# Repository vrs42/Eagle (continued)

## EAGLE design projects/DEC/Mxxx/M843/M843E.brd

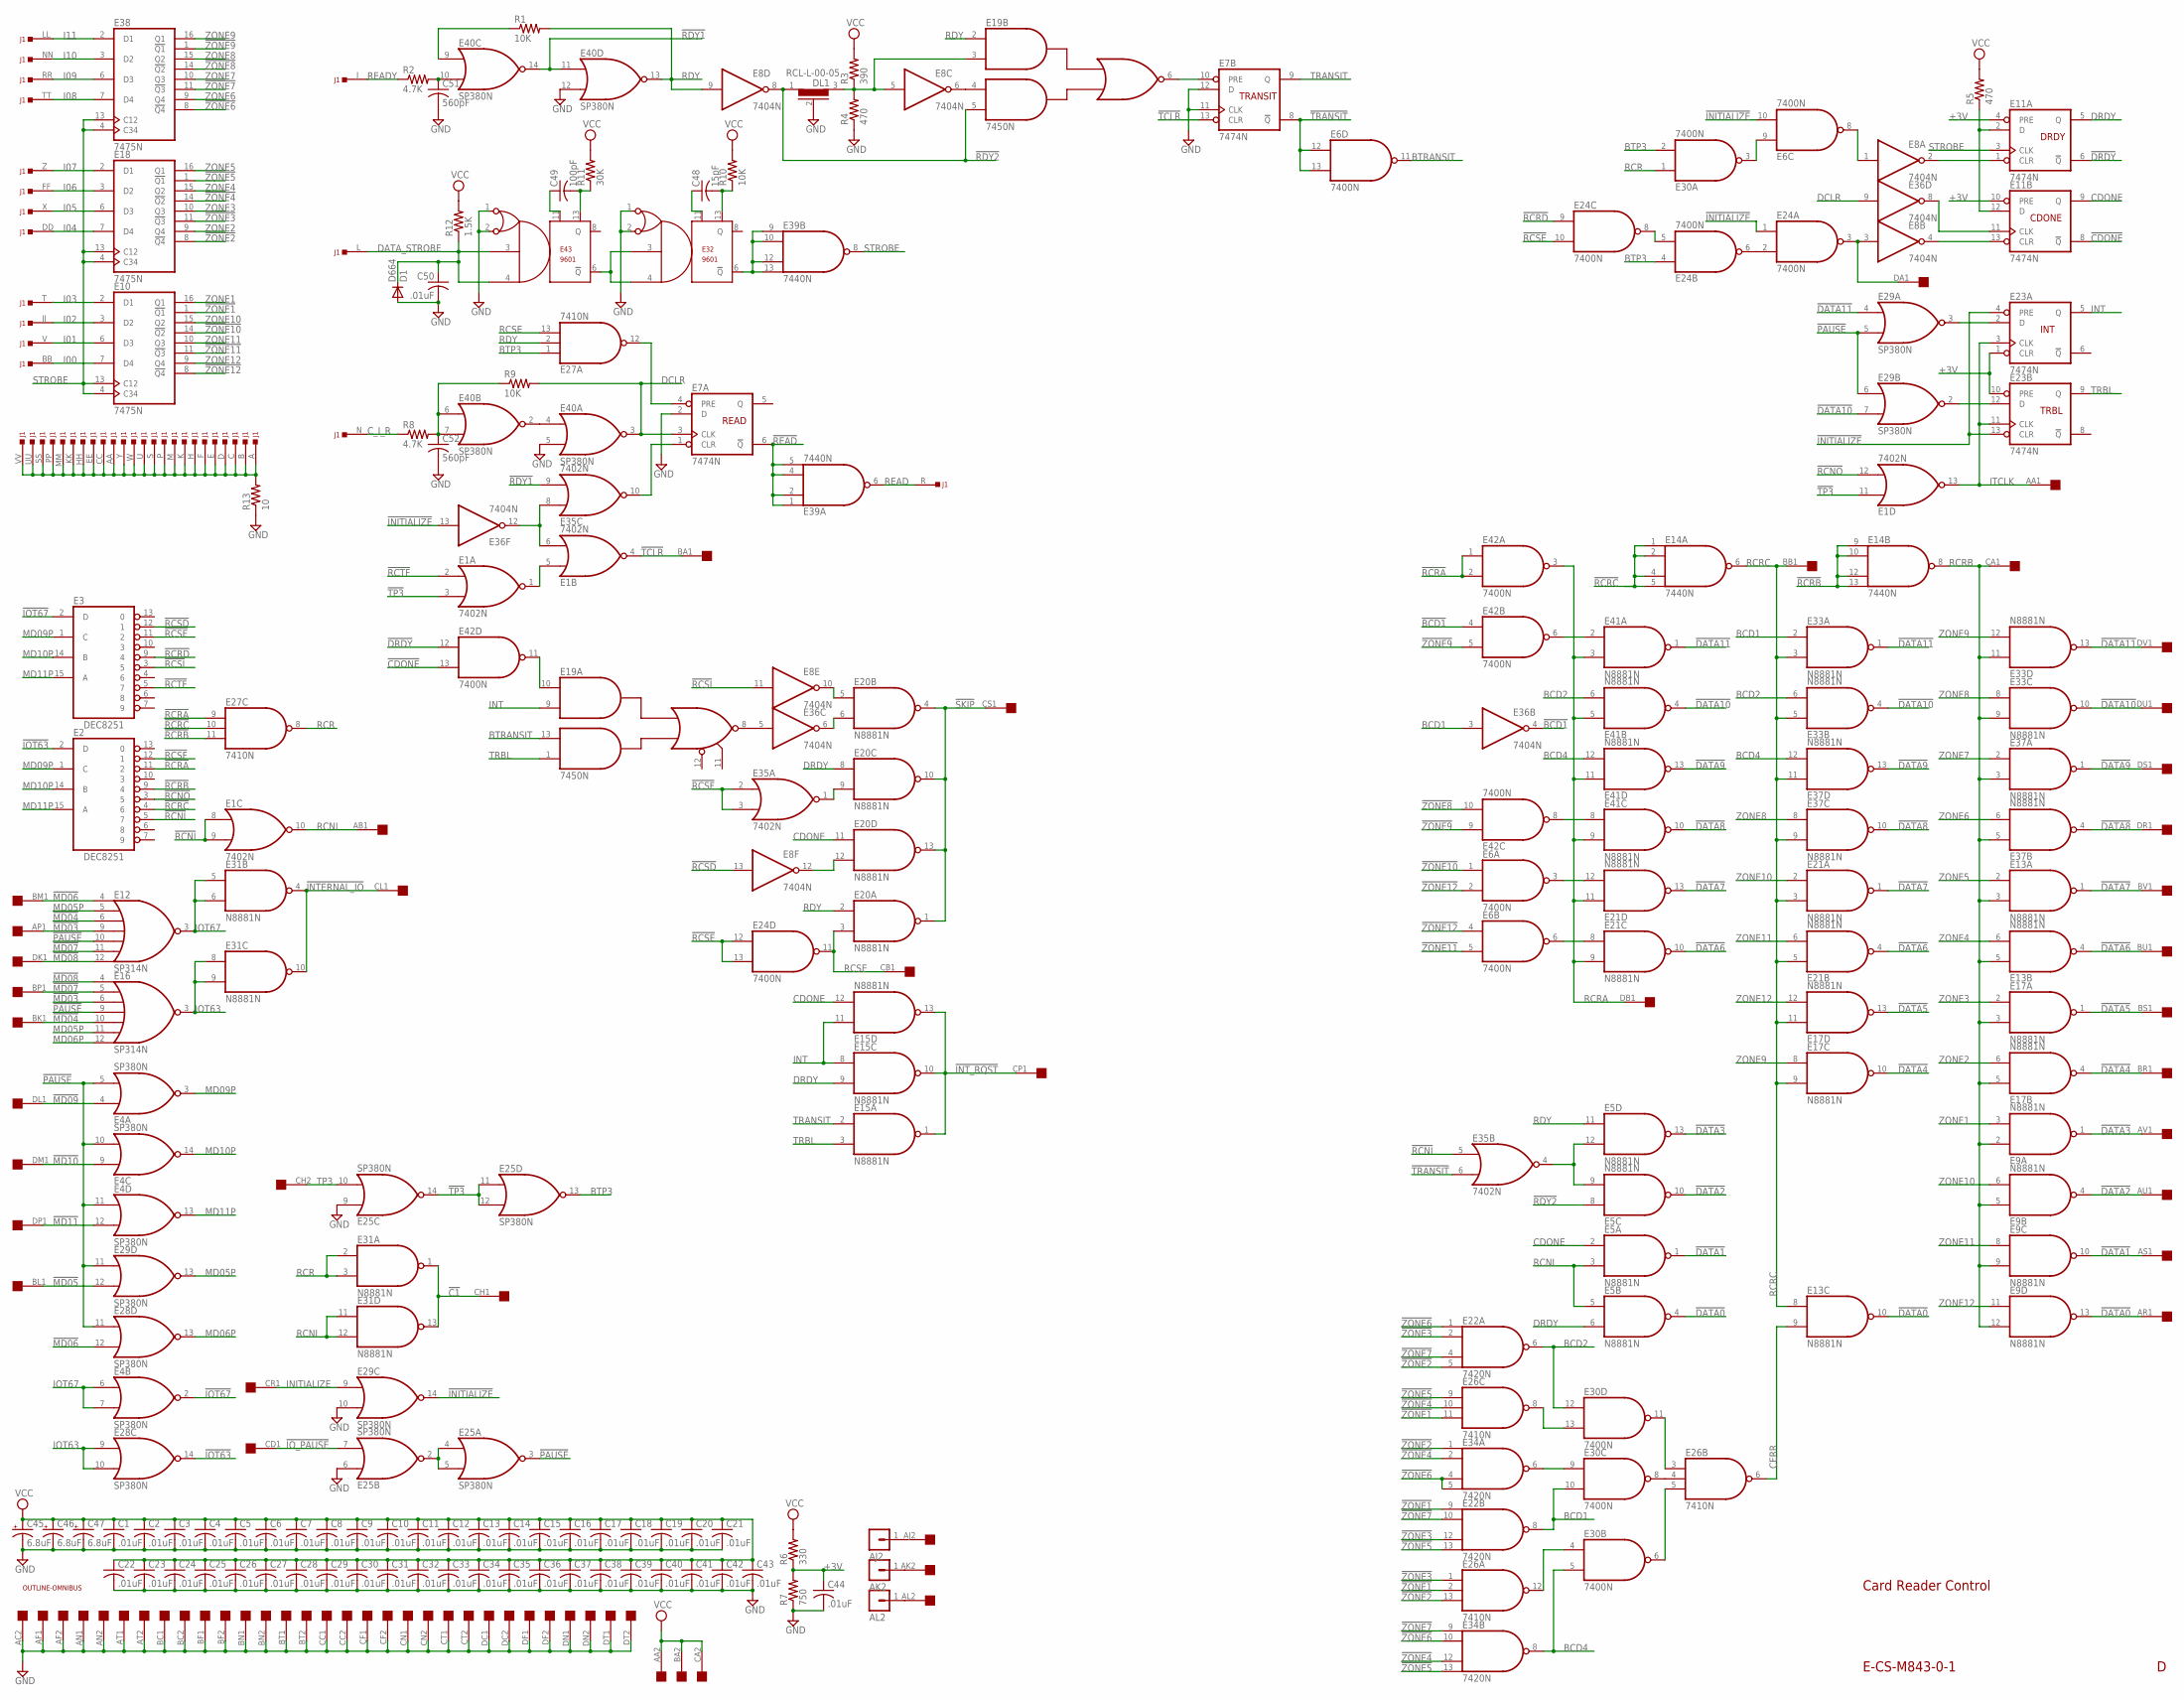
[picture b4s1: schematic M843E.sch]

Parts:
AJ2: MA01-1
AK2: MA01-1
AL2: MA01-1
C1, C6: .01uF; C075-032X103
C2, C3, C4, C5, C7, C8, C9, C10, C11, C12, C13, C14, C15, C16, C17, C18, C19, C20, C21, C22, C23, C24, C25, C26, C27, C28, C29, C30, C31, C32, C33, C34, C35, C36, C37, C38, C39, C40, C41, C42, C43, C44, C50: .01uF; C063-025X075
C45, C46, C47: 6.8uF; E12-8
C48: 15pF; C075-032X103
C49: 100pF; C075-032X103
C51, C52: 560pF; C075-032X103
D1: D664; DO35-10
DL1: RCL-L-00-05
E1, E35: 7402N; DIL14
E2, E3: DEC8251; DIL16
E4, E25, E28, E29, E40: SP380N; DIL14
E5, E9, E13, E15, E17, E20, E21, E31, E33, E37, E41: N8881N; DIL14
E6, E24, E30, E42: 7400N; DIL14
E7, E11, E23: 7474N; DIL14
E8, E36: 7404N; DIL14
E10, E18, E38: 7475N; DIL16
E12, E16: SP314N; DIL14
E14, E39: 7440N; DIL14
E19: 7450N; DIL14
E22, E34: 7420N; DIL14
E26, E27: 7410N; DIL14
E32, E43: 9601; DIL14
EDGE: OMNIBUS; EDGE-CON8
J1: DEC40PINSH; DEC40PINH
R1, R9, R10: 10K; 0207/10
R2, R8: 4.7K; 0207/10
R3: 390; 0207/10
R4, R5: 470; 0207/10
R6: 330; 0207/10
R7: 750; 0207/10
R11: 30K; 0207/10
R12: 1.5K; 0207/10
R13: 10; 0207/10
U$4: OUTLINE-OMNIBUS; OMNIBUS

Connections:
!BCD1: E36.4 (O), E42.4 (I0)
!C1: E31.1 (O), E31.13 (O), EDGE.CH1
!CDONE: E11.8 (!Q), E42.13 (I1)
!DATA0: E5.4 (O), E9.13 (O), E13.10 (O), EDGE.AR1
!DATA1: E5.1 (O), E9.10 (O), EDGE.AS1
!DATA2: E5.10 (O), E9.4 (O), EDGE.AU1
!DATA3: E5.13 (O), E9.1 (O), EDGE.AV1
!DATA4: E17.4 (O), E17.10 (O), EDGE.BR1
!DATA5: E17.1 (O), E17.13 (O), EDGE.BS1
!DATA6: E13.4 (O), E21.4 (O), E21.10 (O), EDGE.BU1
!DATA7: E13.1 (O), E21.1 (O), E21.13 (O), EDGE.BV1
!DATA8: E37.4 (O), E37.10 (O), E41.10 (O), EDGE.DR1
!DATA9: E37.1 (O), E37.13 (O), E41.13 (O), EDGE.DS1
!DATA10: E29.7 (I1), E33.4 (O), E33.10 (O), E41.4 (O), EDGE.DU1
!DATA11: E29.4 (I0), E33.1 (O), E33.13 (O), E41.1 (O), EDGE.DV1
!DRDY: E11.6 (!Q), E42.12 (I0)
!INITIALIZE: E6.10 (I1), E23.4 (PRE), E23.13 (CLR), E24.1 (I0), E29.14 (O), E36.13 (I)
!INTERNAL_IO: E31.4 (O), E31.10 (O), EDGE.CL1
!INT_RQST: E15.1 (O), E15.10 (O), E15.13 (O), EDGE.CP1
!IOT63: E2.2 (D), E28.14 (O)
!IOT67: E3.2 (D), E4.2 (O)
!IO_PAUSE: E25.7 (I1), EDGE.CD1
!MD03: E12.9 (I3), E16.6 (I2), EDGE.AP1
!MD04: E12.6 (I2), E16.10 (I4), EDGE.BK1
!MD05: E29.12 (I1), EDGE.BL1
!MD06: E12.4 (I0), E28.12 (I1), EDGE.BM1
!MD07: E12.11 (I5), E16.5 (I1), EDGE.BP1
!MD08: E12.12 (I6), E16.4 (I0), EDGE.DK1
!MD09: E4.4 (I0), EDGE.DL1
!MD10: E4.9 (I0), EDGE.DM1
!MD11: E4.12 (I1), EDGE.DP1
!PAUSE: E4.5 (I1), E4.10 (I1), E4.11 (I0), E12.10 (I4), E16.9 (I3), E25.3 (O), E28.11 (I0), E29.5 (I1), E29.6 (I0), E29.11 (I0)
!RCNI: E1.8 (I0), E1.9 (I1), E2.5 (7), E35.5 (I0)
!RCNO: E1.12 (I1), E2.3 (5)
!RCRA: E2.11 (2), E27.9 (I0), E42.1 (I0), E42.2 (I1)
!RCRB: E2.9 (4), E14.9 (I0), E14.10 (I1), E14.12 (I2), E14.13 (I3), E27.11 (I2)
!RCRC: E2.4 (6), E14.1 (I0), E14.2 (I1), E14.4 (I2), E14.5 (I3), E27.10 (I1)
!RCRD: E3.9 (4), E24.9 (I0)
!RCSD: E3.12 (1), E8.13 (I)
!RCSE: E3.11 (2), E24.10 (I1), E24.12 (I0), E24.13 (I1)
!RCSF: E2.12 (1), E35.2 (I0), E35.3 (I1)
!RCSI: E3.3 (5), E8.11 (I)
!RCTF: E1.2 (I0), E3.5 (7)
!RDY1: E35.9 (I1), E40.11 (I0), E40.14 (O)
!RDY2: DL1.1, E5.8 (I0), E8.8 (O), E19.5 (I4)
!READ: E7.6 (!Q), E39.1 (I0), E39.2 (I1), E39.4 (I2), E39.5 (I3)
!SKIP: E20.1 (O), E20.4 (O), E20.10 (O), E20.13 (O), EDGE.CS1
!TCLR: E1.4 (O), E7.13 (CLR), EDGE.BA1
!TP3: E1.3 (I1), E1.11 (I0), E25.11 (I0), E25.12 (I1), E25.14 (O)
!TRANSIT: E6.12 (I0), E6.13 (I1), E7.8 (!Q), E35.6 (I1)
!ZONE1: E10.1 (!Q1), E22.9 (I0), E26.2 (I1), E26.11 (I2)
!ZONE2: E18.8 (!Q4), E22.5 (I3), E26.13 (I2), E34.1 (I0)
!ZONE3: E18.11 (!Q3), E22.2 (I1), E22.12 (I2), E26.1 (I0)
!ZONE4: E18.14 (!Q2), E26.10 (I1), E34.2 (I1), E34.12 (I2)
!ZONE5: E18.1 (!Q1), E22.13 (I3), E26.9 (I0), E34.13 (I3)
!ZONE6: E22.1 (I0), E34.4 (I2), E34.5 (I3), E34.10 (I1), E38.8 (!Q4)
!ZONE7: E22.4 (I2), E22.10 (I1), E34.9 (I0), E38.11 (!Q3)
!ZONE8: E38.14 (!Q2), E42.10 (I1)
!ZONE9: E38.1 (!Q1), E42.5 (I1), E42.9 (I0)
!ZONE10: E6.1 (I0), E10.14 (!Q2)
!ZONE11: E6.5 (I1), E10.11 (!Q3)
!ZONE12: E6.2 (I1), E6.4 (I0), E10.8 (!Q4)
+3V: C44.1, E11.4 (PRE), E11.10 (PRE), E23.1 (CLR), E23.10 (PRE), R6.1, R7.2
AJ2: AJ2.1, EDGE.AJ2
AK2: AK2.1, EDGE.AK2
AL2: AL2.1, EDGE.AL2
BCD1: E22.8 (O), E30.10 (I1), E33.2 (I0), E36.3 (I)
BCD2: E22.6 (O), E30.12 (I0), E33.6 (I1), E41.6 (I1)
BCD4: E30.5 (I1), E34.8 (O), E37.12 (I1), E41.12 (I1)
BTP3: E24.4 (I0), E25.13 (O), E27.1 (I0), E30.2 (I1)
BTRANSIT: E6.11 (O), E19.13 (I3)
CDONE: E5.2 (I0), E11.9 (Q), E15.12 (I1), E20.11 (I0)
CERR: E13.9 (I1), E26.6 (O)
C_I_R: J1.N, R8.1
DATA_STROBE: C50.1, D1.C, E43.3, E43.4, J1.L, R12.1
DCLR: E7.3 (CLK), E36.9 (I), E40.3 (O), R9.2
DRDY: E5.6 (I1), E11.5 (Q), E15.9 (I1), E20.8 (I0)
GND: C1.2, C2.2, C3.2, C4.2, C5.2, C6.2, C7.2, C8.2, C9.2, C10.2, C11.2, C12.2, C13.2, C14.2, C15.2, C16.2, C17.2, C18.2, C19.2, C20.2, C21.2, C22.2, C23.2, C24.2, C25.2, C26.2, C27.2, C28.2, C29.2, C30.2, C31.2, C32.2, C33.2, C34.2, C35.2, C36.2, C37.2, C38.2, C39.2, C40.2, C41.2, C42.2, C43.2, C44.2, C45.-, C46.-, C47.-, C50.2, C51.2, C52.2, D1.A, DL1.2, E1.7 (GND), E2.8 (GND), E3.8 (GND), E4.1 (GND), E5.7 (GND), E6.7 (GND), E7.2 (D), E7.7 (GND), E7.11 (CLK), E7.12 (D), E8.7 (GND), E9.7 (GND), E10.12 (GND), E11.7 (GND), E12.1 (GND), E13.7 (GND), E14.7 (GND), E15.7 (GND), E16.1 (GND), E17.7 (GND), E18.12 (GND), E19.7 (GND), E20.7 (GND), E21.7 (GND), E22.7 (GND), E23.7 (GND), E24.7 (GND), E25.1 (GND), E25.6 (I0), E25.9 (I0), E26.7 (GND), E27.7 (GND), E28.1 (GND), E29.1 (GND), E29.10 (I1), E30.7 (GND), E31.7 (GND), E32.1, E32.2, E32.7 (GND), E33.7 (GND), E34.7 (GND), E35.7 (GND), E36.7 (GND), E37.7 (GND), E38.12 (GND), E39.7 (GND), E40.1 (GND), E40.5 (I1), E40.12 (I1), E41.7 (GND), E42.7 (GND), E43.1, E43.2, E43.7 (GND), EDGE.AC2, EDGE.AF1, EDGE.AF2, EDGE.AN1, EDGE.AN2, EDGE.AT1, EDGE.AT2, EDGE.BC1, EDGE.BC2, EDGE.BF1, EDGE.BF2, EDGE.BN1, EDGE.BN2, EDGE.BT1, EDGE.BT2, EDGE.CC1, EDGE.CC2, EDGE.CF1, EDGE.CF2, EDGE.CN1, EDGE.CN2, EDGE.CT1, EDGE.CT2, EDGE.DC1, EDGE.DC2, EDGE.DF1, EDGE.DF2, EDGE.DN1, EDGE.DN2, EDGE.DT1, EDGE.DT2, R4.1, R7.1, R13.1
I00: E10.7 (D4), J1.BB
I01: E10.6 (D3), J1.V
I02: E10.3 (D2), J1.JJ
I03: E10.2 (D1), J1.T
I04: E18.7 (D4), J1.DD
I05: E18.6 (D3), J1.X
I06: E18.3 (D2), J1.FF
I07: E18.2 (D1), J1.Z
I08: E38.7 (D4), J1.TT
I09: E38.6 (D3), J1.RR
I10: E38.3 (D2), J1.NN
I11: E38.2 (D1), J1.LL
INITIALIZE: E29.9 (I0), EDGE.CR1
INT: E15.8 (I0), E15.11 (I0), E19.9 (I2), E23.5 (Q)
IOT63: E16.3 (O), E28.9 (I0), E28.10 (I1), E31.8 (I0), E31.9 (I1)
IOT67: E4.6 (I0), E4.7 (I1), E12.3 (O), E31.5 (I0), E31.6 (I1)
ITCLK: E1.13 (O), E23.3 (CLK), E23.11 (CLK), EDGE.AA1
MD05P: E12.5 (I1), E16.11 (I5), E29.13 (O)
MD06P: E16.12 (I6), E28.13 (O)
MD09P: E2.1 (C), E3.1 (C), E4.3 (O)
MD10P: E2.14 (B), E3.14 (B), E4.14 (O)
MD11P: E2.15 (A), E3.15 (A), E4.13 (O)
unnamed: E26.3 (I0), E30.11 (O)
unnamed: E25.2 (O), E25.4 (I0), E25.5 (I1)
unnamed: E11.11 (CLK), E36.8 (O)
unnamed: E6.8 (O), E8.1 (I)
unnamed: E5.9 (I1), E5.12 (I1), E35.4 (O)
unnamed: E32.6 (!Q), E39.9 (I0), E39.10 (I1), E39.12 (I2), E39.13 (I3)
unnamed: E32.3, E32.4, E43.6 (!Q)
unnamed: E26.4 (I1), E30.8 (O)
unnamed: C49.2, E43.13, R11.1
unnamed: E30.9 (I0), E34.6 (O)
unnamed: C49.1, E43.11
unnamed: C48.2, E32.13, R10.1
unnamed: C52.1, E40.6 (I0), E40.7 (I1), R8.2, R9.1
unnamed: C48.1, E32.11
unnamed: E19.8 (O), E36.5 (I)
unnamed: E40.2 (O), E40.4 (I0)
unnamed: C51.1, E40.10 (I1), R2.2
unnamed: E26.5 (I2), E30.6 (O)
unnamed: E6.3 (O), E21.12 (I1)
unnamed: E41.2 (I0), E42.6 (O)
unnamed: DL1.3, E8.5 (I), E19.3 (I2), R3.1, R4.2
unnamed: E6.6 (O), E21.8 (I0)
unnamed: E41.8 (I0), E42.8 (O)
unnamed: E40.9 (I0), R1.1
unnamed: E8.6 (O), E19.4 (I3)
unnamed: E8.4 (O), E11.13 (CLR)
unnamed: E8.3 (I), E24.3 (O), EDGE.DA1
unnamed: E6.9 (I0), E30.3 (O)
unnamed: E8.2 (O), E11.1 (CLR)
unnamed: E7.10 (PRE), E19.6 (O)
unnamed: E26.12 (O), E30.4 (I0)
unnamed: E26.8 (O), E30.13 (I1)
unnamed: E11.2 (D), E11.12 (D), R5.1
unnamed: E7.1 (CLR), E35.10 (O)
unnamed: J1.A, J1.AA, J1.B, J1.C, J1.CC, J1.D, J1.E, J1.EE, J1.F, J1.H, J1.HH, J1.K, J1.KK, J1.M, J1.MM, J1.P, J1.PP, J1.S, J1.SS, J1.U, J1.UU, J1.VV, J1.W, J1.Y, R13.2
unnamed: E23.2 (D), E29.3 (O)
unnamed: E7.4 (PRE), E27.12 (O)
unnamed: E20.6 (I1), E36.6 (O)
unnamed: E19.10 (I1), E42.11 (O)
unnamed: E24.2 (I1), E24.6 (O)
unnamed: E20.9 (I1), E35.1 (O)
unnamed: E8.12 (O), E20.12 (I1)
unnamed: E1.6 (I1), E35.8 (I0), E36.12 (O)
unnamed: E23.12 (D), E29.2 (O)
unnamed: E1.1 (O), E1.5 (I0)
unnamed: E24.5 (I1), E24.8 (O)
RCNI: E1.10 (O), E5.3 (I1), E5.5 (I0), E31.11 (I0), E31.12 (I1), EDGE.AB1
RCR: E27.8 (O), E30.1 (I0), E31.2 (I0), E31.3 (I1)
RCRA: E21.9 (I1), E21.11 (I0), E41.3 (I1), E41.5 (I0), E41.9 (I1), E41.11 (I0), E42.3 (O), EDGE.DB1
RCRB: E9.2 (I0), E9.5 (I0), E9.9 (I1), E9.12 (I1), E13.3 (I1), E13.5 (I0), E14.8 (O), E17.3 (I1), E17.5 (I0), E33.9 (I1), E33.11 (I0), E37.3 (I1), E37.5 (I0), EDGE.CA1
RCRC: E13.8 (I0), E14.6 (O), E17.9 (I1), E17.11 (I0), E21.3 (I1), E21.5 (I0), E33.3 (I1), E33.5 (I0), E37.9 (I1), E37.11 (I0), EDGE.BB1
RCSE: E20.3 (I1), E24.11 (O), E27.13 (I2), EDGE.CB1
RCSI: E8.10 (O), E20.5 (I0)
RDY: E5.11 (I0), E8.9 (I), E19.2 (I1), E20.2 (I0), E27.2 (I1), E40.13 (O), R1.2
READ: E39.6 (O), J1.R
READY: J1.J, R2.1
STROBE: E10.4 (C34), E10.13 (C12), E11.3 (CLK), E18.4 (C34), E18.13 (C12), E38.4 (C34), E38.13 (C12), E39.8 (O)
TP3: E25.10 (I1), EDGE.CH2
TRANSIT: E7.9 (Q), E15.2 (I0)
TRBL: E15.3 (I1), E19.1 (I4), E23.9 (Q)
VCC: C1.1, C2.1, C3.1, C4.1, C5.1, C6.1, C7.1, C8.1, C9.1, C10.1, C11.1, C12.1, C13.1, C14.1, C15.1, C16.1, C17.1, C18.1, C19.1, C20.1, C21.1, C22.1, C23.1, C24.1, C25.1, C26.1, C27.1, C28.1, C29.1, C30.1, C31.1, C32.1, C33.1, C34.1, C35.1, C36.1, C37.1, C38.1, C39.1, C40.1, C41.1, C42.1, C43.1, C45.+, C46.+, C47.+, E1.14 (VCC), E2.16 (VCC), E3.16 (VCC), E4.8 (VCC), E5.14 (VCC), E6.14 (VCC), E7.14 (VCC), E8.14 (VCC), E9.14 (VCC), E10.5 (VCC), E11.14 (VCC), E12.8 (VCC), E13.14 (VCC), E14.14 (VCC), E15.14 (VCC), E16.8 (VCC), E17.14 (VCC), E18.5 (VCC), E19.14 (VCC), E20.14 (VCC), E21.14 (VCC), E22.14 (VCC), E23.14 (VCC), E24.14 (VCC), E25.8 (VCC), E26.14 (VCC), E27.14 (VCC), E28.8 (VCC), E29.8 (VCC), E30.14 (VCC), E31.14 (VCC), E32.14 (VCC), E33.14 (VCC), E34.14 (VCC), E35.14 (VCC), E36.14 (VCC), E37.14 (VCC), E38.5 (VCC), E39.14 (VCC), E40.8 (VCC), E41.14 (VCC), E42.14 (VCC), E43.14 (VCC), EDGE.AA2, EDGE.BA2, EDGE.CA2, R3.2, R5.2, R6.2, R10.2, R11.2, R12.2
ZONE1: E9.3 (I1), E10.16 (Q1)
ZONE2: E17.6 (I1), E18.9 (Q4)
ZONE3: E17.2 (I0), E18.10 (Q3)
ZONE4: E13.6 (I1), E18.15 (Q2)
ZONE5: E13.2 (I0), E18.16 (Q1)
ZONE6: E37.6 (I1), E38.9 (Q4)
ZONE7: E37.2 (I0), E38.10 (Q3)
ZONE8: E33.8 (I0), E37.8 (I0), E38.15 (Q2)
ZONE9: E17.8 (I0), E33.12 (I1), E38.16 (Q1)
ZONE10: E9.6 (I1), E10.15 (Q2), E21.2 (I0)
ZONE11: E9.8 (I0), E10.10 (Q3), E21.6 (I1)
ZONE12: E9.11 (I0), E10.9 (Q4), E17.12 (I1)

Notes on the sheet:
E-CS-M843-0-1
Card Reader Control
TRBL
INT
TRANSIT
CDONE
DRDY
READ

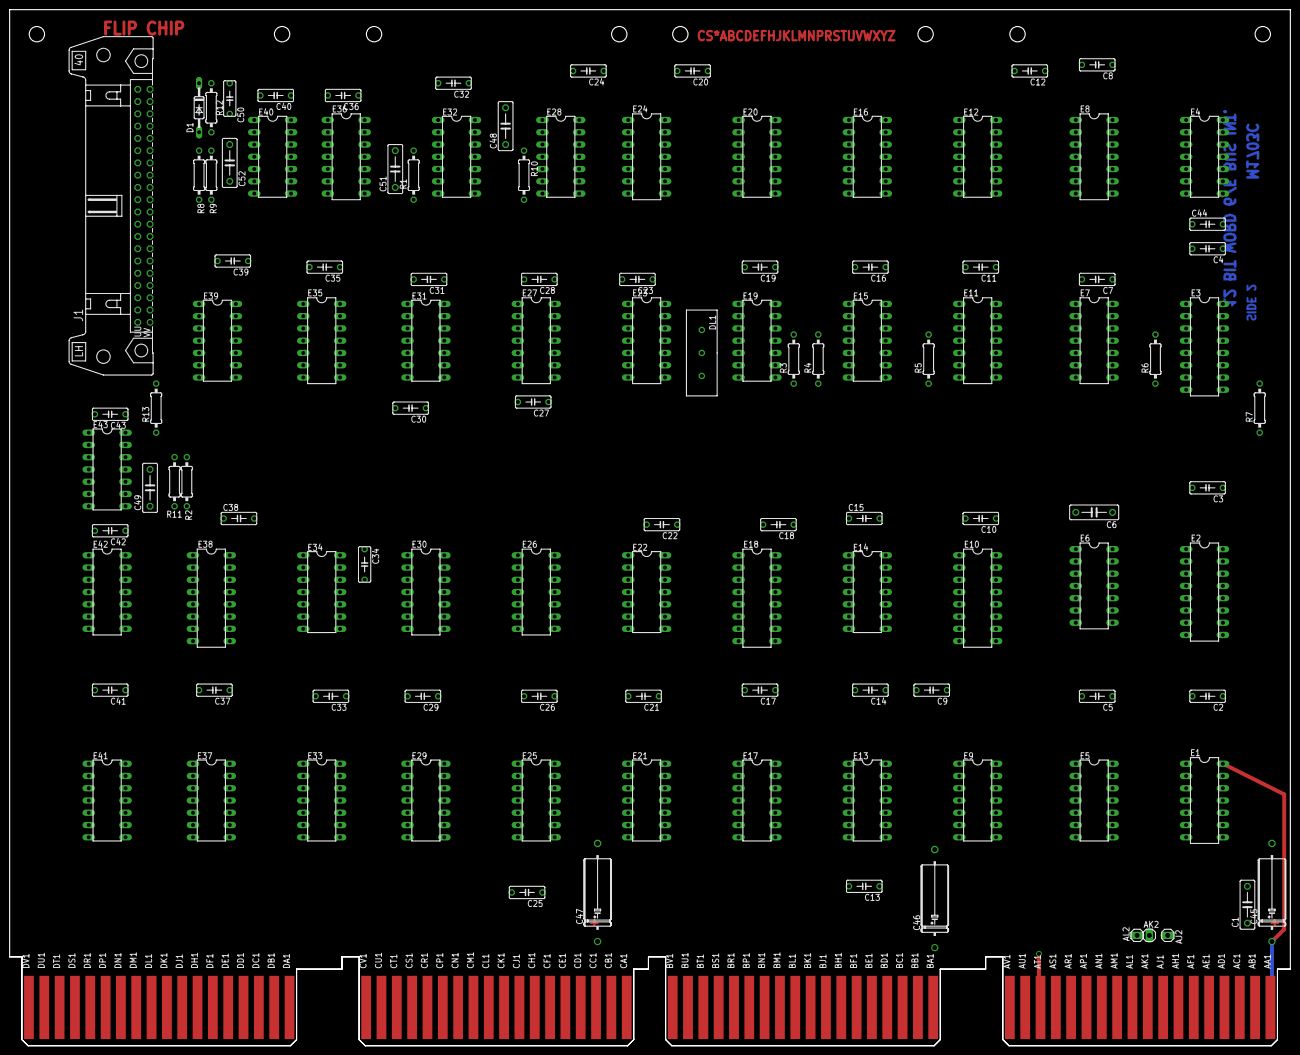
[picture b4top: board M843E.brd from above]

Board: 2 copper layers, 265.3 x 214.6 mm, 117 parts (0 on the bottom side), 173 nets.

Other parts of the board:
U$3: FLIPCHIP

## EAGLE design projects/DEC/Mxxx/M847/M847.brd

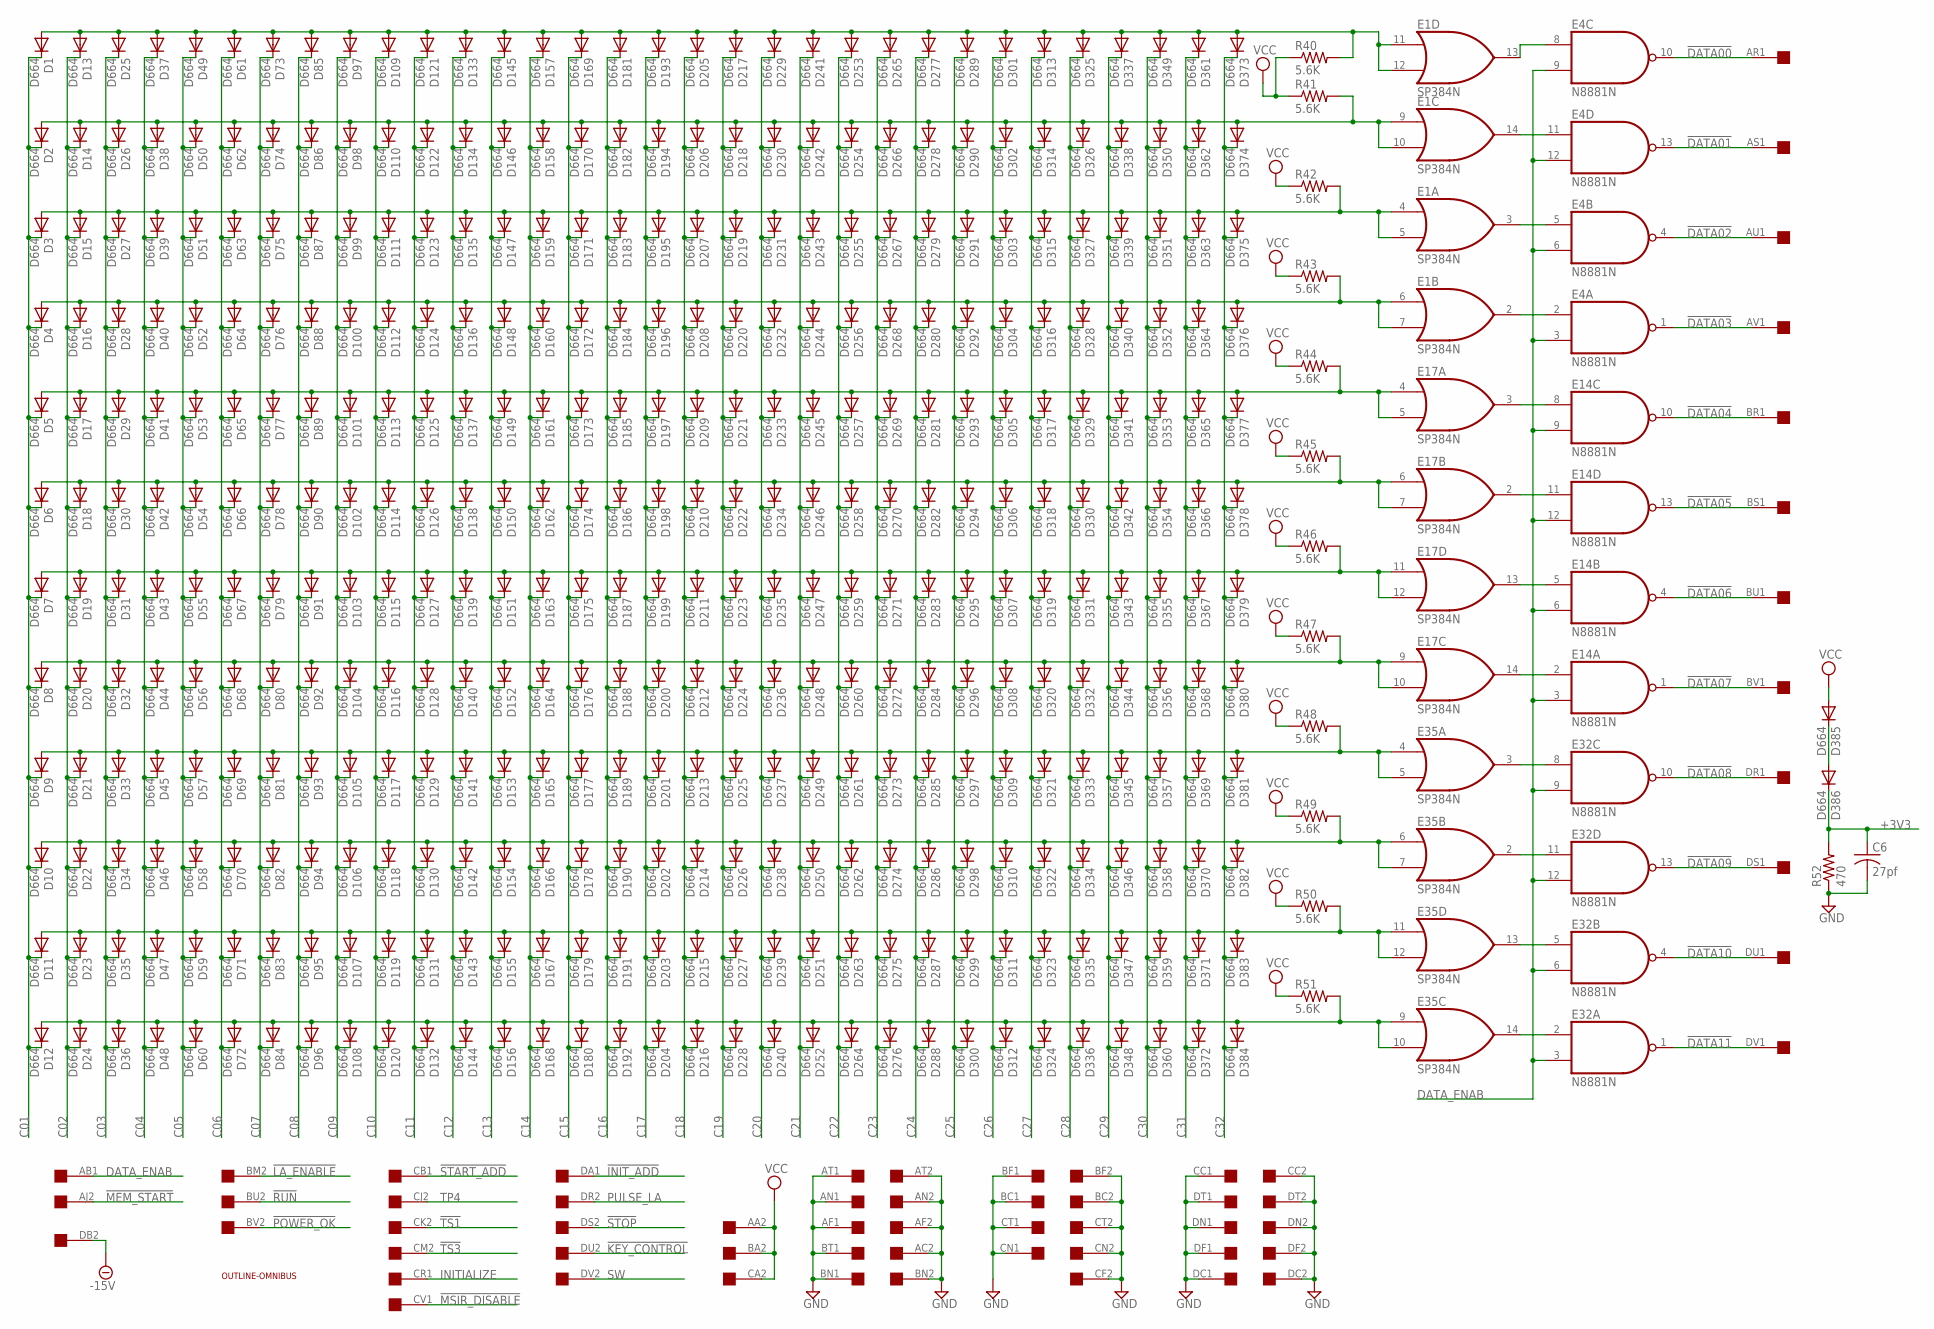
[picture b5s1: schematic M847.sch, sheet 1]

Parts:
C6: 27pf; C050-025X075
D1, D2, D3, D4, D5, D6, D7, D8, D9, D10, D11, D12, D13, D14, D15, D16, D17, D18, D19, D20, D21, D22, D23, D24, D25, D26, D27, D28, D29, D30, D31, D32, D33, D34, D35, D36, D37, D38, D39, D40, D41, D42, D43, D44, D45, D46, D47, D48, D49, D50, D51, D52, D53, D54, D55, D56, D57, D58, D59, D60, D61, D62, D63, D64, D65, D66, D67, D68, D69, D70, D71, D72, D73, D74, D75, D76, D77, D78, D79, D80, D81, D82, D83, D84, D85, D86, D87, D88, D89, D90, D91, D92, D93, D94, D95, D96, D97, D98, D99, D100, D101, D102, D103, D104, D105, D106, D107, D108, D109, D110, D111, D112, D113, D114, D115, D116, D117, D118, D119, D120, D121, D122, D123, D124, D125, D126, D127, D128, D129, D130, D131, D132, D133, D134, D135, D136, D137, D138, D139, D140, D141, D142, D143, D144, D145, D146, D147, D148, D149, D150, D151, D152, D153, D154, D155, D156, D157, D158, D159, D160, D161, D162, D163, D164, D165, D166, D167, D168, D169, D170, D171, D172, D173, D174, D175, D176, D177, D178, D179, D180, D181, D182, D183, D184, D185, D186, D187, D188, D189, D190, D191, D192, D193, D194, D195, D196, D197, D198, D199, D200, D201, D202, D203, D204, D205, D206, D207, D208, D209, D210, D211, D212, D213, D214, D215, D216, D217, D218, D219, D220, D221, D222, D223, D224, D225, D226, D227, D228, D229, D230, D231, D232, D233, D234, D235, D236, D237, D238, D239, D240, D241, D242, D243, D244, D245, D246, D247, D248, D249, D250, D251, D252, D253, D254, D255, D256, D257, D258, D259, D260, D261, D262, D263, D264, D265, D266, D267, D268, D269, D270, D271, D272, D273, D274, D275, D276, D277, D278, D279, D280, D281, D282, D283, D284, D285, D286, D287, D288, D289, D290, D291, D292, D293, D294, D295, D296, D297, D298, D299, D300, D301, D302, D303, D304, D305, D306, D307, D308, D309, D310, D311, D312, D313, D314, D315, D316, D317, D318, D319, D320, D321, D322, D323, D324, D325, D326, D327, D328, D329, D330, D331, D332, D333, D334, D335, D336, D337, D338, D339, D340, D341, D342, D343, D344, D345, D346, D347, D348, D349, D350, D351, D352, D353, D354, D355, D356, D357, D358, D359, D360, D361, D362, D363, D364, D365, D366, D367, D368, D369, D370, D371, D372, D373, D374, D375, D376, D377, D378, D379, D380, D381, D382, D383, D384, D385, D386: D664; DO35-10
E1, E17, E35: SP384N; DIL14
E4, E14, E32: N8881N; DIL14
R40, R41, R42, R43, R44, R45, R46, R47, R48, R49, R50, R51: 5.6K; 0207/10
R52: 470; 0207/10
U$1: OUTLINE-OMNIBUS; OMNIBUS
U$2: QUAD; EDGE-CON8

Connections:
!DATA00: E4.10 (O), U$2.AR1; also elsewhere on the board
!DATA01: E4.13 (O), U$2.AS1; also elsewhere on the board
!DATA02: E4.4 (O), U$2.AU1; also elsewhere on the board
!DATA03: E4.1 (O), U$2.AV1; also elsewhere on the board
!DATA04: E14.10 (O), U$2.BR1; also elsewhere on the board
!DATA05: E14.13 (O), U$2.BS1; also elsewhere on the board
!DATA06: E14.4 (O), U$2.BU1; also elsewhere on the board
!DATA07: E14.1 (O), U$2.BV1; also elsewhere on the board
!DATA08: E32.10 (O), U$2.DR1; also elsewhere on the board
!DATA09: E32.13 (O), U$2.DS1; also elsewhere on the board
!DATA10: E32.4 (O), U$2.DU1; also elsewhere on the board
!DATA11: E32.1 (O), U$2.DV1; also elsewhere on the board
!INIT_ADD: U$2.DA1; also elsewhere on the board
!KEY_CONTROL: U$2.DU2; also elsewhere on the board
!LA_ENABLE: U$2.BM2; also elsewhere on the board
!MEM_START: U$2.AJ2; also elsewhere on the board
!MSIR_DISABLE: U$2.CV1; also elsewhere on the board
!POWER_OK: U$2.BV2; also elsewhere on the board
!RUN: U$2.BU2; also elsewhere on the board
!START_ADD: U$2.CB1; also elsewhere on the board
!STOP: U$2.DS2; also elsewhere on the board
!TS1: U$2.CK2; also elsewhere on the board
!TS3: U$2.CM2; also elsewhere on the board
+3V3: C6.1, D386.C, R52.2; also elsewhere on the board
-15V: U$2.DB2; also elsewhere on the board
C01: D1.C, D2.C, D3.C, D4.C, D5.C, D6.C, D7.C, D8.C, D9.C, D10.C, D11.C, D12.C; also elsewhere on the board
C02: D13.C, D14.C, D15.C, D16.C, D17.C, D18.C, D19.C, D20.C, D21.C, D22.C, D23.C, D24.C; also elsewhere on the board
C03: D25.C, D26.C, D27.C, D28.C, D29.C, D30.C, D31.C, D32.C, D33.C, D34.C, D35.C, D36.C; also elsewhere on the board
C04: D37.C, D38.C, D39.C, D40.C, D41.C, D42.C, D43.C, D44.C, D45.C, D46.C, D47.C, D48.C; also elsewhere on the board
C05: D49.C, D50.C, D51.C, D52.C, D53.C, D54.C, D55.C, D56.C, D57.C, D58.C, D59.C, D60.C; also elsewhere on the board
C06: D61.C, D62.C, D63.C, D64.C, D65.C, D66.C, D67.C, D68.C, D69.C, D70.C, D71.C, D72.C; also elsewhere on the board
C07: D73.C, D74.C, D75.C, D76.C, D77.C, D78.C, D79.C, D80.C, D81.C, D82.C, D83.C, D84.C; also elsewhere on the board
C08: D85.C, D86.C, D87.C, D88.C, D89.C, D90.C, D91.C, D92.C, D93.C, D94.C, D95.C, D96.C; also elsewhere on the board
C09: D97.C, D98.C, D99.C, D100.C, D101.C, D102.C, D103.C, D104.C, D105.C, D106.C, D107.C, D108.C; also elsewhere on the board
C10: D109.C, D110.C, D111.C, D112.C, D113.C, D114.C, D115.C, D116.C, D117.C, D118.C, D119.C, D120.C; also elsewhere on the board
C11: D121.C, D122.C, D123.C, D124.C, D125.C, D126.C, D127.C, D128.C, D129.C, D130.C, D131.C, D132.C; also elsewhere on the board
C12: D133.C, D134.C, D135.C, D136.C, D137.C, D138.C, D139.C, D140.C, D141.C, D142.C, D143.C, D144.C; also elsewhere on the board
C13: D145.C, D146.C, D147.C, D148.C, D149.C, D150.C, D151.C, D152.C, D153.C, D154.C, D155.C, D156.C; also elsewhere on the board
C14: D157.C, D158.C, D159.C, D160.C, D161.C, D162.C, D163.C, D164.C, D165.C, D166.C, D167.C, D168.C; also elsewhere on the board
C15: D169.C, D170.C, D171.C, D172.C, D173.C, D174.C, D175.C, D176.C, D177.C, D178.C, D179.C, D180.C; also elsewhere on the board
C16: D181.C, D182.C, D183.C, D184.C, D185.C, D186.C, D187.C, D188.C, D189.C, D190.C, D191.C, D192.C; also elsewhere on the board
C17: D193.C, D194.C, D195.C, D196.C, D197.C, D198.C, D199.C, D200.C, D201.C, D202.C, D203.C, D204.C; also elsewhere on the board
C18: D205.C, D206.C, D207.C, D208.C, D209.C, D210.C, D211.C, D212.C, D213.C, D214.C, D215.C, D216.C; also elsewhere on the board
C19: D217.C, D218.C, D219.C, D220.C, D221.C, D222.C, D223.C, D224.C, D225.C, D226.C, D227.C, D228.C; also elsewhere on the board
C20: D229.C, D230.C, D231.C, D232.C, D233.C, D234.C, D235.C, D236.C, D237.C, D238.C, D239.C, D240.C; also elsewhere on the board
C21: D241.C, D242.C, D243.C, D244.C, D245.C, D246.C, D247.C, D248.C, D249.C, D250.C, D251.C, D252.C; also elsewhere on the board
C22: D253.C, D254.C, D255.C, D256.C, D257.C, D258.C, D259.C, D260.C, D261.C, D262.C, D263.C, D264.C; also elsewhere on the board
C23: D265.C, D266.C, D267.C, D268.C, D269.C, D270.C, D271.C, D272.C, D273.C, D274.C, D275.C, D276.C; also elsewhere on the board
C24: D277.C, D278.C, D279.C, D280.C, D281.C, D282.C, D283.C, D284.C, D285.C, D286.C, D287.C, D288.C; also elsewhere on the board
C25: D289.C, D290.C, D291.C, D292.C, D293.C, D294.C, D295.C, D296.C, D297.C, D298.C, D299.C, D300.C; also elsewhere on the board
C26: D301.C, D302.C, D303.C, D304.C, D305.C, D306.C, D307.C, D308.C, D309.C, D310.C, D311.C, D312.C; also elsewhere on the board
C27: D313.C, D314.C, D315.C, D316.C, D317.C, D318.C, D319.C, D320.C, D321.C, D322.C, D323.C, D324.C; also elsewhere on the board
C28: D325.C, D326.C, D327.C, D328.C, D329.C, D330.C, D331.C, D332.C, D333.C, D334.C, D335.C, D336.C; also elsewhere on the board
C29: D337.C, D338.C, D339.C, D340.C, D341.C, D342.C, D343.C, D344.C, D345.C, D346.C, D347.C, D348.C; also elsewhere on the board
C30: D349.C, D350.C, D351.C, D352.C, D353.C, D354.C, D355.C, D356.C, D357.C, D358.C, D359.C, D360.C; also elsewhere on the board
C31: D361.C, D362.C, D363.C, D364.C, D365.C, D366.C, D367.C, D368.C, D369.C, D370.C, D371.C, D372.C; also elsewhere on the board
C32: D373.C, D374.C, D375.C, D376.C, D377.C, D378.C, D379.C, D380.C, D381.C, D382.C, D383.C, D384.C; also elsewhere on the board
DATA_ENAB: E4.3 (I1), E4.6 (I1), E4.9 (I1), E4.12 (I1), E14.3 (I1), E14.6 (I1), E14.9 (I1), E14.12 (I1), E32.3 (I1), E32.6 (I1), E32.9 (I1), E32.12 (I1), U$2.AB1; also elsewhere on the board
GND: C6.2, E1.1 (GND), E4.7 (GND), E14.7 (GND), E17.1 (GND), E32.7 (GND), E35.1 (GND), R52.1, U$2.AC2, U$2.AF1, U$2.AF2, U$2.AN1, U$2.AN2, U$2.AT1, U$2.AT2, U$2.BC1, U$2.BC2, U$2.BF1, U$2.BF2, U$2.BN1, U$2.BN2, U$2.BT1, U$2.CC1, U$2.CC2, U$2.CF2, U$2.CN1, U$2.CN2, U$2.CT1, U$2.CT2, U$2.DC1, U$2.DC2, U$2.DF1, U$2.DF2, U$2.DN1, U$2.DN2, U$2.DT1, U$2.DT2; also elsewhere on the board
INITIALIZE: U$2.CR1; also elsewhere on the board
unnamed: D1.A, D13.A, D25.A, D37.A, D49.A, D61.A, D73.A, D85.A, D97.A, D109.A, D121.A, D133.A, D145.A, D157.A, D169.A, D181.A, D193.A, D205.A, D217.A, D229.A, D241.A, D253.A, D265.A, D277.A, D289.A, D301.A, D313.A, D325.A, D337.A, D349.A, D361.A, D373.A, E1.11 (I0), E1.12 (I1), R40.2
unnamed: D12.A, D24.A, D36.A, D48.A, D60.A, D72.A, D84.A, D96.A, D108.A, D120.A, D132.A, D144.A, D156.A, D168.A, D180.A, D192.A, D204.A, D216.A, D228.A, D240.A, D252.A, D264.A, D276.A, D288.A, D300.A, D312.A, D324.A, D336.A, D348.A, D360.A, D372.A, D384.A, E35.9 (I0), E35.10 (I1), R51.2
unnamed: D11.A, D23.A, D35.A, D47.A, D59.A, D71.A, D83.A, D95.A, D107.A, D119.A, D131.A, D143.A, D155.A, D167.A, D179.A, D191.A, D203.A, D215.A, D227.A, D239.A, D251.A, D263.A, D275.A, D287.A, D299.A, D311.A, D323.A, D335.A, D347.A, D359.A, D371.A, D383.A, E35.11 (I0), E35.12 (I1), R50.2
unnamed: D10.A, D22.A, D34.A, D46.A, D58.A, D70.A, D82.A, D94.A, D106.A, D118.A, D130.A, D142.A, D154.A, D166.A, D178.A, D190.A, D202.A, D214.A, D226.A, D238.A, D250.A, D262.A, D274.A, D286.A, D298.A, D310.A, D322.A, D334.A, D346.A, D358.A, D370.A, D382.A, E35.6 (I0), E35.7 (I1), R49.2
unnamed: D8.A, D20.A, D32.A, D44.A, D56.A, D68.A, D80.A, D92.A, D104.A, D116.A, D128.A, D140.A, D152.A, D164.A, D176.A, D188.A, D200.A, D212.A, D224.A, D236.A, D248.A, D260.A, D272.A, D284.A, D296.A, D308.A, D320.A, D332.A, D344.A, D356.A, D368.A, D380.A, E17.9 (I0), E17.10 (I1), R47.2
unnamed: D7.A, D19.A, D31.A, D43.A, D55.A, D67.A, D79.A, D91.A, D103.A, D115.A, D127.A, D139.A, D151.A, D163.A, D175.A, D187.A, D199.A, D211.A, D223.A, D235.A, D247.A, D259.A, D271.A, D283.A, D295.A, D307.A, D319.A, D331.A, D343.A, D355.A, D367.A, D379.A, E17.11 (I0), E17.12 (I1), R46.2
unnamed: D9.A, D21.A, D33.A, D45.A, D57.A, D69.A, D81.A, D93.A, D105.A, D117.A, D129.A, D141.A, D153.A, D165.A, D177.A, D189.A, D201.A, D213.A, D225.A, D237.A, D249.A, D261.A, D273.A, D285.A, D297.A, D309.A, D321.A, D333.A, D345.A, D357.A, D369.A, D381.A, E35.4 (I0), E35.5 (I1), R48.2
unnamed: D6.A, D18.A, D30.A, D42.A, D54.A, D66.A, D78.A, D90.A, D102.A, D114.A, D126.A, D138.A, D150.A, D162.A, D174.A, D186.A, D198.A, D210.A, D222.A, D234.A, D246.A, D258.A, D270.A, D282.A, D294.A, D306.A, D318.A, D330.A, D342.A, D354.A, D366.A, D378.A, E17.6 (I0), E17.7 (I1), R45.2
unnamed: D5.A, D17.A, D29.A, D41.A, D53.A, D65.A, D77.A, D89.A, D101.A, D113.A, D125.A, D137.A, D149.A, D161.A, D173.A, D185.A, D197.A, D209.A, D221.A, D233.A, D245.A, D257.A, D269.A, D281.A, D293.A, D305.A, D317.A, D329.A, D341.A, D353.A, D365.A, D377.A, E17.4 (I0), E17.5 (I1), R44.2
unnamed: D4.A, D16.A, D28.A, D40.A, D52.A, D64.A, D76.A, D88.A, D100.A, D112.A, D124.A, D136.A, D148.A, D160.A, D172.A, D184.A, D196.A, D208.A, D220.A, D232.A, D244.A, D256.A, D268.A, D280.A, D292.A, D304.A, D316.A, D328.A, D340.A, D352.A, D364.A, D376.A, E1.6 (I0), E1.7 (I1), R43.2
unnamed: D3.A, D15.A, D27.A, D39.A, D51.A, D63.A, D75.A, D87.A, D99.A, D111.A, D123.A, D135.A, D147.A, D159.A, D171.A, D183.A, D195.A, D207.A, D219.A, D231.A, D243.A, D255.A, D267.A, D279.A, D291.A, D303.A, D315.A, D327.A, D339.A, D351.A, D363.A, D375.A, E1.4 (I0), E1.5 (I1), R42.2
unnamed: D2.A, D14.A, D26.A, D38.A, D50.A, D62.A, D74.A, D86.A, D98.A, D110.A, D122.A, D134.A, D146.A, D158.A, D170.A, D182.A, D194.A, D206.A, D218.A, D230.A, D242.A, D254.A, D266.A, D278.A, D290.A, D302.A, D314.A, D326.A, D338.A, D350.A, D362.A, D374.A, E1.9 (I0), E1.10 (I1), R41.2
unnamed: E14.5 (I0), E17.13 (O)
unnamed: E14.11 (I0), E17.2 (O)
unnamed: E14.8 (I0), E17.3 (O)
unnamed: E1.2 (O), E4.2 (I0)
unnamed: E1.3 (O), E4.5 (I0)
unnamed: E1.14 (O), E4.11 (I0)
unnamed: E1.13 (O), E4.8 (I0)
unnamed: E32.2 (I0), E35.14 (O)
unnamed: E32.5 (I0), E35.13 (O)
unnamed: E32.11 (I0), E35.2 (O)
unnamed: E32.8 (I0), E35.3 (O)
unnamed: E14.2 (I0), E17.14 (O)
unnamed: D385.C, D386.A
PULSE_LA: U$2.DR2; also elsewhere on the board
SW: U$2.DV2; also elsewhere on the board
TP4: U$2.CJ2; also elsewhere on the board
VCC: D385.A, E1.8 (VCC), E4.14 (VCC), E14.14 (VCC), E17.8 (VCC), E32.14 (VCC), E35.8 (VCC), R40.1, R41.1, R42.1, R43.1, R44.1, R45.1, R46.1, R47.1, R48.1, R49.1, R50.1, R51.1, U$2.AA2, U$2.BA2, U$2.CA2; also elsewhere on the board
